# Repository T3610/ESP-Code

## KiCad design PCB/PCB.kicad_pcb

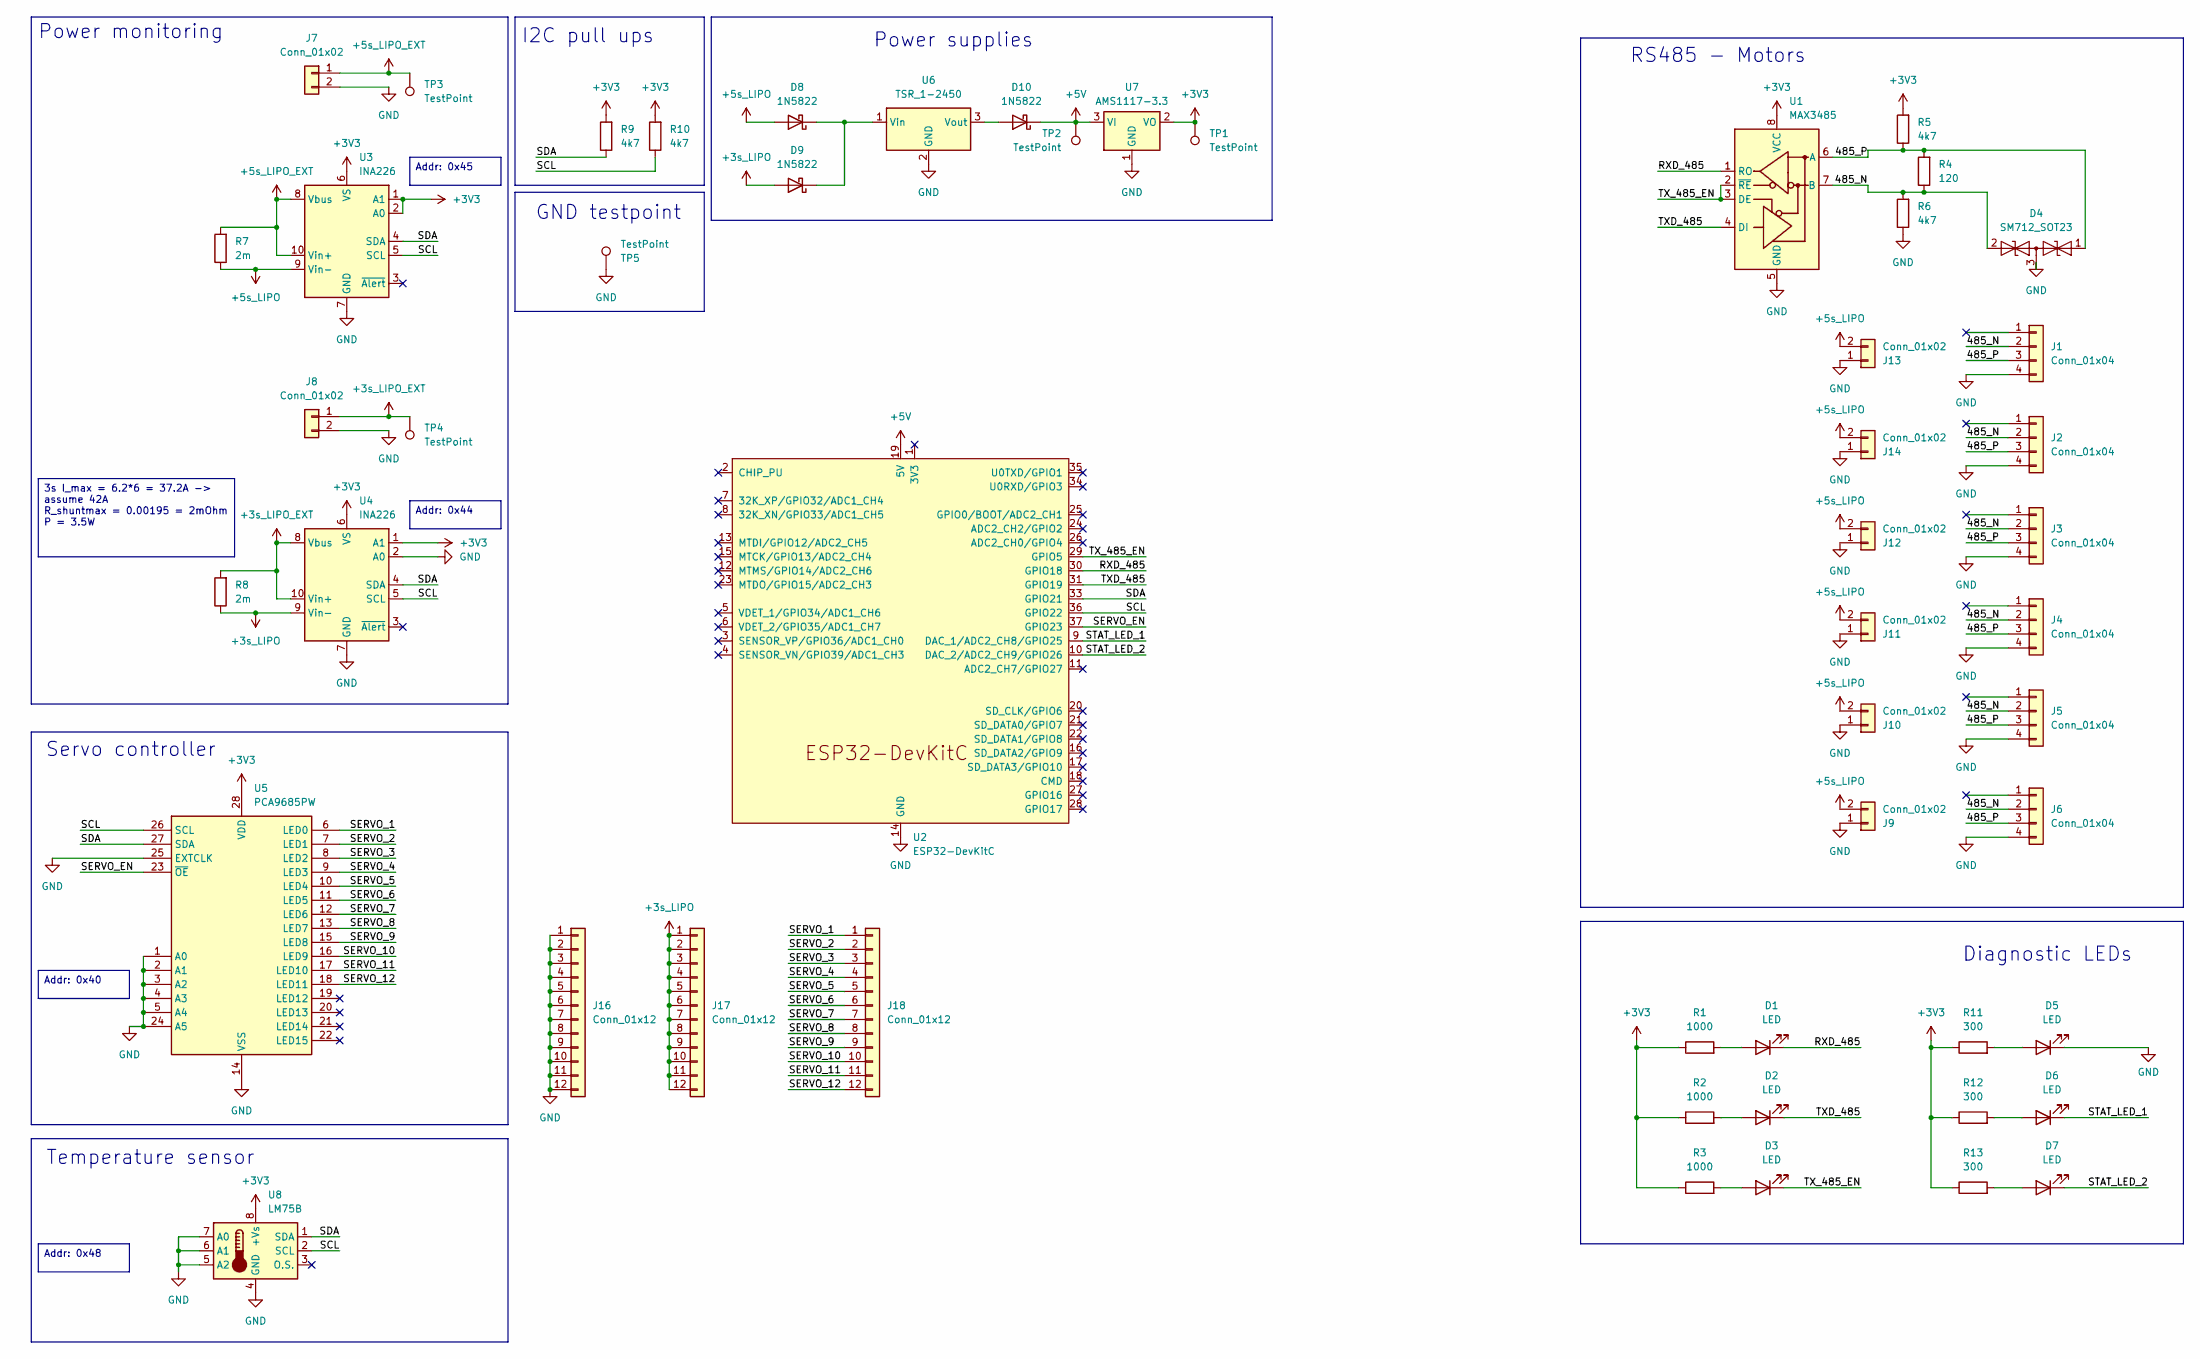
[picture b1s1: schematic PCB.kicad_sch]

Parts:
D1, D2, D3, D5, D6, D7: LED; LED_D5.0mm
D4: SM712_SOT23; SOT-23
D8, D9, D10: 1N5822; D_DO-201AD_P15.24mm_Horizontal
J1, J2, J3, J4, J5, J6: Conn_01x04; JST_ZH_B4B-ZR_1x04_P1.50mm_Vertical
J7, J8: Conn_01x02; AMASS_XT60-M_1x02_P7.20mm_Vertical
J9, J10, J11, J12, J13, J14: Conn_01x02; JST_XH_B2B-XH-AM_1x02_P2.50mm_Vertical
J16, J17, J18: Conn_01x12; PinHeader_1x12_P2.54mm_Vertical
R1, R2, R3: 1000; R_Axial_DIN0207_L6.3mm_D2.5mm_P10.16mm_Horizontal
R4: 120; R_Axial_DIN0207_L6.3mm_D2.5mm_P10.16mm_Horizontal
R5, R6, R9, R10: 4k7; R_Axial_DIN0207_L6.3mm_D2.5mm_P10.16mm_Horizontal
R7, R8: 2m; R_2512_6332Metric_Pad1.40x3.35mm_HandSolder
R11, R12, R13: 300; R_Axial_DIN0207_L6.3mm_D2.5mm_P10.16mm_Horizontal
TP1, TP2, TP3, TP4: TestPoint; TestPoint_Pad_D2.0mm
TP5: TestPoint; TestPoint_Pad_2.0x2.0mm
U1: MAX3485; SOIC-8_3.9x4.9mm_P1.27mm
U2: ESP32-DevKitC
U3, U4: INA226; TSSOP-10_3x3mm_P0.5mm
U5: PCA9685PW; TSSOP-28_4.4x9.7mm_P0.65mm
U6: TSR_1-2450; Converter_DCDC_TRACO_TSR-1_THT
U7: AMS1117-3.3; SOT-223-3_TabPin2
U8: LM75B; SOIC-8_3.9x4.9mm_P1.27mm

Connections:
+3V3: R1.1, R2.1, R3.1, R5.2, R9.2, R10.2, R11.1, R12.1, R13.1, TP1.1 (1_1), U1.8 (VCC), U3.1 (A1), U3.2 (A0), U3.6 (VS), U4.1 (A1), U4.6 (VS), U5.28 (VDD), U7.2 (VO), U8.8 (+Vs)
+3s_LIPO: D9.2 (A), J17.1, J17.2, J17.3, J17.4, J17.5, J17.6, J17.7, J17.8, J17.9, J17.10, J17.11, J17.12, R8.1, U4.9 (Vin-)
+3s_LIPO_EXT: J8.1, R8.2, TP4.1 (1_1), U4.8 (Vbus), U4.10 (Vin+)
+5V: D10.1 (K), TP2.1 (1_1), U2.19 (5V), U7.3 (VI)
+5s_LIPO: D8.2 (A), J9.2, J10.2, J11.2, J12.2, J13.2, J14.2, R7.1, U3.9 (Vin-)
+5s_LIPO_EXT: J7.1, R7.2, TP3.1 (1_1), U3.8 (Vbus), U3.10 (Vin+)
/485_N: D4.2 (A2), J1.2, J2.2, J3.2, J4.2, J5.2, J6.2, R4.1, R6.2, U1.7 (B)
/485_P: D4.1 (A1), J1.3, J2.3, J3.3, J4.3, J5.3, J6.3, R4.2, R5.1, U1.6 (A)
/RXD_485: D1.1 (K), U1.1 (RO), U2.30 (GPIO18)
/SCL: R10.1, U2.36 (GPIO22), U3.5 (SCL), U4.5 (SCL), U5.26 (SCL), U8.2 (SCL)
/SDA: R9.1, U2.33 (GPIO21), U3.4 (SDA), U4.4 (SDA), U5.27 (SDA), U8.1 (SDA)
/SERVO_1: J18.1, U5.6 (LED0)
/SERVO_2: J18.2, U5.7 (LED1)
/SERVO_3: J18.3, U5.8 (LED2)
/SERVO_4: J18.4, U5.9 (LED3)
/SERVO_5: J18.5, U5.10 (LED4)
/SERVO_6: J18.6, U5.11 (LED5)
/SERVO_7: J18.7, U5.12 (LED6)
/SERVO_8: J18.8, U5.13 (LED7)
/SERVO_9: J18.9, U5.15 (LED8)
/SERVO_10: J18.10, U5.16 (LED9)
/SERVO_11: J18.11, U5.17 (LED10)
/SERVO_12: J18.12, U5.18 (LED11)
/SERVO_EN: U2.37 (GPIO23), U5.23 (~OE)
/STAT_LED_1: D6.1 (K), U2.9 (DAC_1/ADC2_CH8/GPIO25)
/STAT_LED_2: D7.1 (K), U2.10 (DAC_2/ADC2_CH9/GPIO26)
/TXD_485: D2.1 (K), U1.4 (DI), U2.31 (GPIO19)
/TX_485_EN: D3.1 (K), U1.2 (~RE), U1.3 (DE), U2.29 (GPIO5)
GND: D4.3 (common), D5.1 (K), J1.4, J2.4, J3.4, J4.4, J5.4, J6.4, J7.2, J8.2, J9.1, J10.1, J11.1, J12.1, J13.1, J14.1, J16.1, J16.2, J16.3, J16.4, J16.5, J16.6, J16.7, J16.8, J16.9, J16.10, J16.11, J16.12, R6.1, TP5.1 (1_1), U1.5 (GND), U2.14 (GND), U2.32 (GND), U2.38 (GND), U3.7 (GND), U4.2 (A0), U4.7 (GND), U5.1 (A0), U5.2 (A1), U5.3 (A2), U5.4 (A3), U5.5 (A4), U5.14 (VSS), U5.24 (A5), U5.25 (EXTCLK), U6.2 (GND), U7.1 (GND), U8.4 (GND), U8.5 (A2), U8.6 (A1), U8.7 (A0)
unnamed: D1.2 (A), R1.2
unnamed: D2.2 (A), R2.2
unnamed: D3.2 (A), R3.2
unnamed: D5.2 (A), R11.2
unnamed: D6.2 (A), R12.2
unnamed: D7.2 (A), R13.2
unnamed: D8.1 (K), D9.1 (K), U6.1 (Vin)
unnamed: D10.2 (A), U6.3 (Vout)

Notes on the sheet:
I2C pull ups
Diagnostic LEDs
Temperature sensor
Servo controller
Power supplies
Power monitoring
GND testpoint
RS485 - Motors
3s I_max = 6.2*6 = 37.2A -> assume 42A R_shuntmax = 0.00195 = 2mOhm P = 3.5W
Addr: 0x48
Addr: 0x45
Addr: 0x40
Addr: 0x44

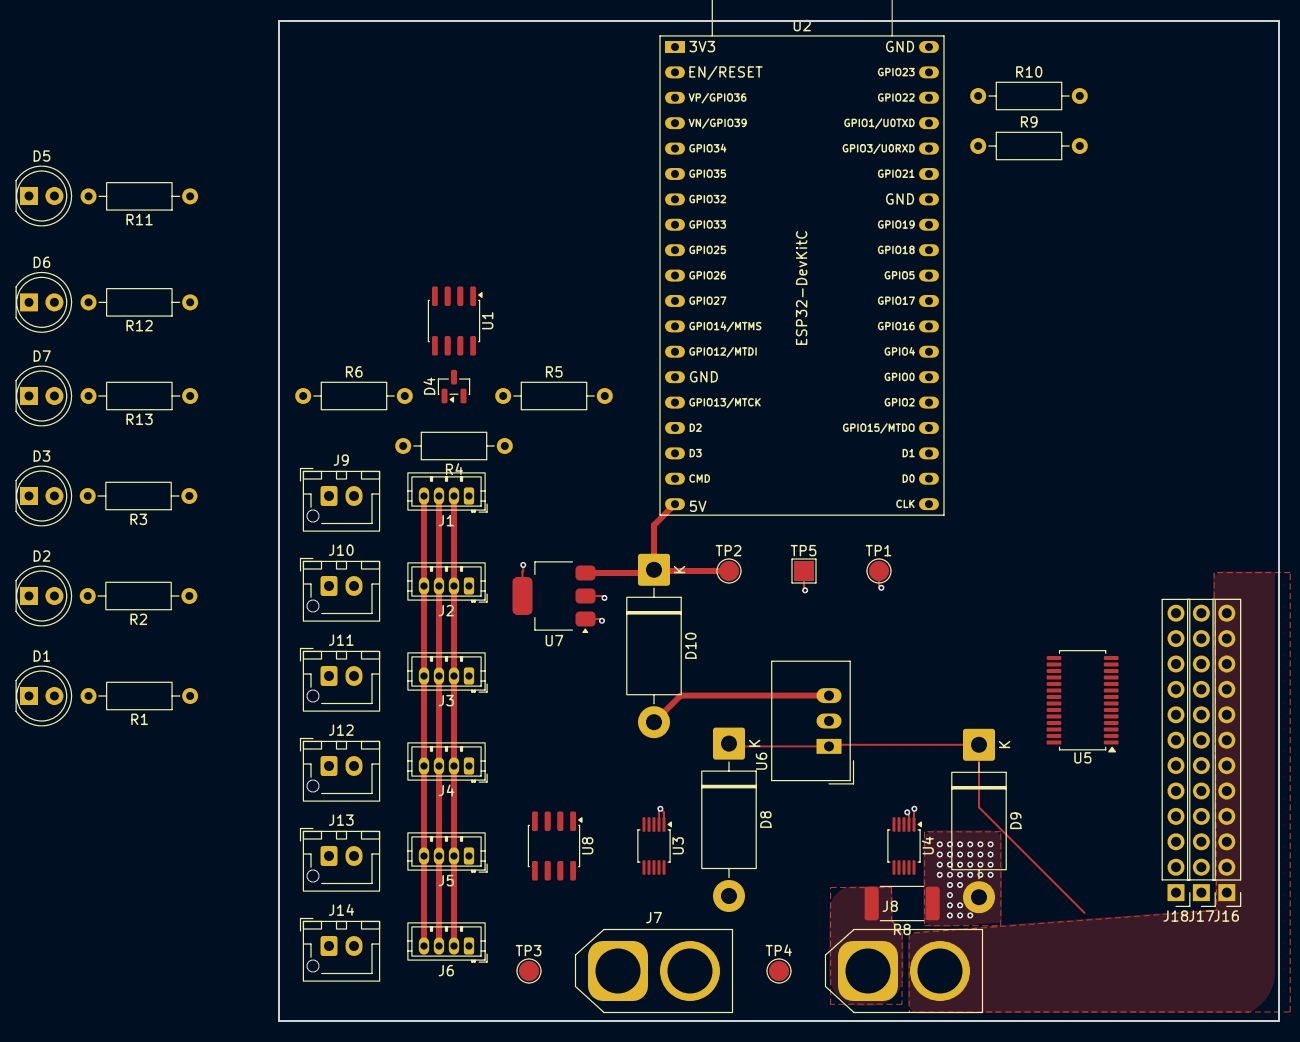
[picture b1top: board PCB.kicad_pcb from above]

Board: 4 copper layers, 100.0 x 100.0 mm, 52 parts (0 on the bottom side), 37 nets.
